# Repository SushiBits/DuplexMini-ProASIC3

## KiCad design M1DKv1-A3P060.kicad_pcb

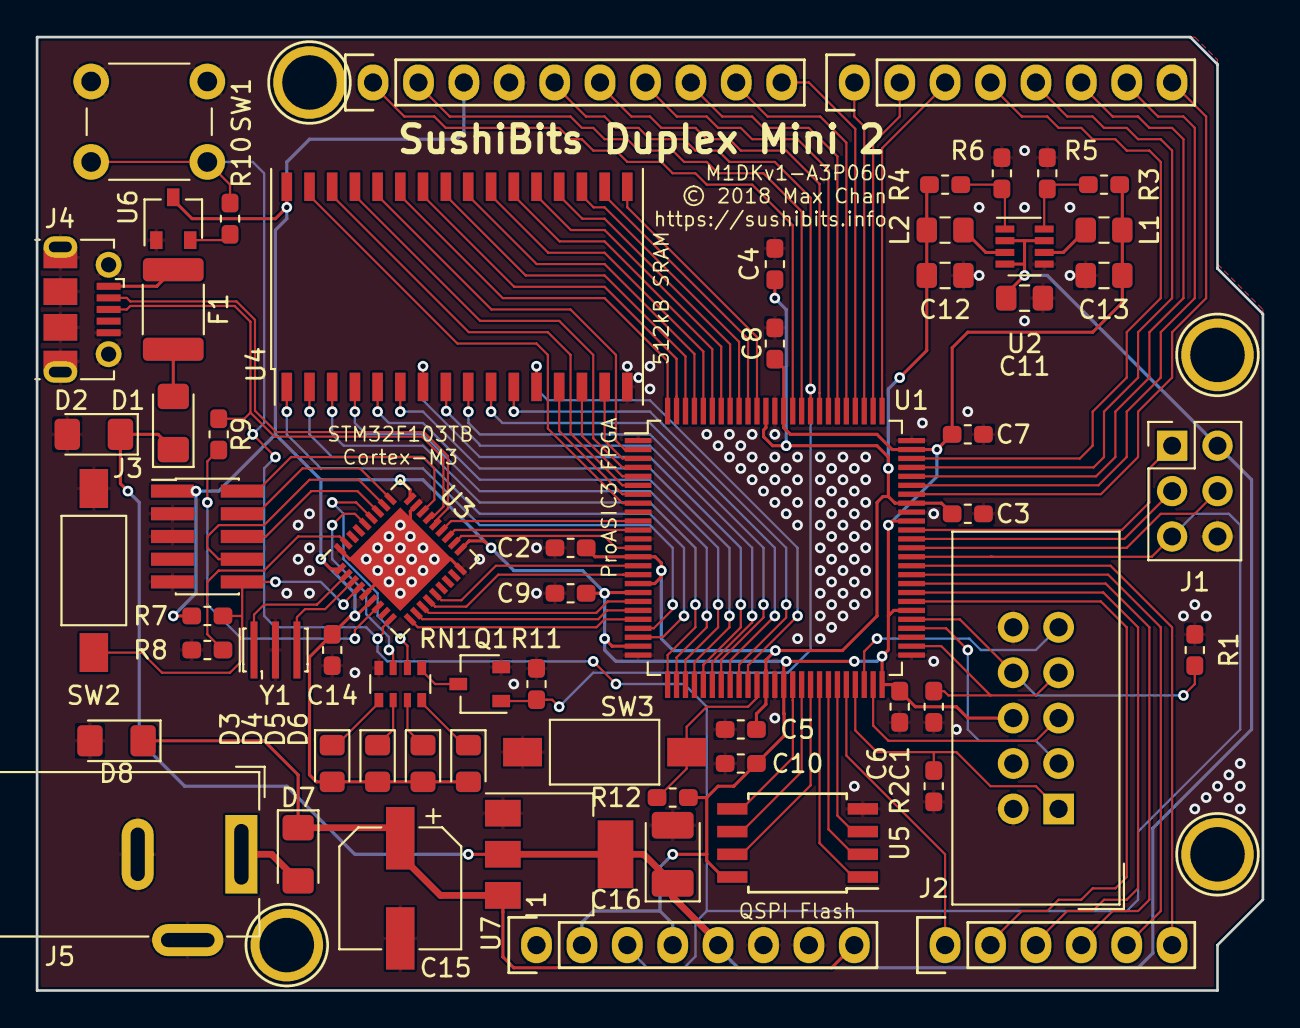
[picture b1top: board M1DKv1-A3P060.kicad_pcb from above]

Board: 2 copper layers, 68.6 x 53.3 mm, 65 parts (0 on the bottom side), 108 nets.

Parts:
C1: 1µ; C_0603_1608Metric_Pad1.05x0.95mm_HandSolder
C2, C3, C4, C5, C6, C7, C8, C9, C10, C14: 100n; C_0603_1608Metric_Pad1.05x0.95mm_HandSolder
C11: 10µ; C_0805_2012Metric_Pad1.15x1.40mm_HandSolder
C12, C13: 47µ; C_0805_2012Metric_Pad1.15x1.40mm_HandSolder
C15: 47µ; CP_Elec_6.3x5.3
C16: 220µ; CP_EIA-3528-12_Kemet-T_Pad1.50x2.35mm_HandSolder
D1: DSK14; D_1206_3216Metric_Pad1.42x1.75mm_HandSolder
D2: SMF5.0A; D_1206_3216Metric_Pad1.42x1.75mm_HandSolder
D3: Power; LED_0805_2012Metric_Pad1.15x1.40mm_HandSolder
D4: RX; LED_0805_2012Metric_Pad1.15x1.40mm_HandSolder
D5: TX; LED_0805_2012Metric_Pad1.15x1.40mm_HandSolder
D6: L; LED_0805_2012Metric_Pad1.15x1.40mm_HandSolder
D7: DSK10; D_1206_3216Metric_Pad1.42x1.75mm_HandSolder
D8: SMF12A; D_1206_3216Metric_Pad1.42x1.75mm_HandSolder
F1: 500mA; Fuse_1812_4532Metric_Pad1.30x3.40mm_HandSolder
J1: SPI; PinHeader_2x03_P2.54mm_Vertical
J2: FPGA; IDC-Header_2x05_P2.54mm_Vertical
J3: ARM; PinHeader_2x05_P1.27mm_Vertical_SMD
J4: USB; USB_Micro-B_Molex-105017-0001
J5: 12V; BarrelJack_Wuerth_6941xx301002
L1: 4.7µ; L_0805_2012Metric_Pad1.15x1.40mm_HandSolder
L2: 2.2µ; L_0805_2012Metric_Pad1.15x1.40mm_HandSolder
P1: Power; Socket_Strip_Arduino_1x08
P2: Analog; Socket_Strip_Arduino_1x06
P3: Digital; Socket_Strip_Arduino_1x10
P4: Digital; Socket_Strip_Arduino_1x08
P5, P6, P7, P8: CONN_01X01; Arduino_1pin
Q1: 2N7002; SOT-23W
R1, R2, R7, R8, R11, R12: 10k; R_0603_1608Metric_Pad1.05x0.95mm_HandSolder
R3, R4: 16k; R_0603_1608Metric_Pad1.05x0.95mm_HandSolder
R5: 3.6k; R_0603_1608Metric_Pad1.05x0.95mm_HandSolder
R6: 1.1k; R_0603_1608Metric_Pad1.05x0.95mm_HandSolder
R9: 1.5k; R_0603_1608Metric_Pad1.05x0.95mm_HandSolder
R10: 4.7k; R_0603_1608Metric_Pad1.05x0.95mm_HandSolder
RN1: 510; R_Array_Convex_4x0603
SW1: Reset; SW_PUSH_6mm
SW2: MCU Reset; SW_SPST_FSMSM
SW3: Action; SW_SPST_FSMSM
U1: A3P060-VQG100; TQFP-100_14x14mm_P0.5mm
U2: MP2122; SOT-23-8
U3: STM32F103TBUx; QFN-36-1EP_6x6mm_P0.5mm_EP4.1x4.1mm
U4: AS6C4008; TSOP-II-32_21.0x10.2mm_P1.27mm
U5: 25Q80; SOIJ-8_5.3x5.3mm_P1.27mm
U6: TCM809; SOT-23W
U7: LM1117-3.3; SOT-223-3_TabPin2
Y1: 16M; Resonator_SMD_muRata_CSTxExxV-3Pin_3.0x1.1mm_HandSoldering

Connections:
+1V5: C2.1, C3.1, C4.1, C5.1, C12.1, L2.2, R4.1, U1.14, U1.17, U1.37, U1.68, U1.89
+3V3: C6.1, C7.1, C8.1, C9.1, C10.1, C13.1, C14.2, D3.2, D4.2, D5.2, D6.2, J2.6, J3.1, L1.2, P1.2, P1.4, P3.3, R3.1, R7.1, R12.2, U1.18, U1.24, U1.39, U1.50, U1.56, U1.66, U1.74, U1.87, U3.1, U3.6, U3.19, U3.27, U4.32, U5.8, U6.3
+5V: C11.1, C16.1, D1.1, D2.1, J1.2, P1.5, U2.2, U2.4, U2.7, U7.2
+12V: C15.1, D7.1, D8.1, P1.8, U7.3
/0(Rx): P4.8, U1.69
/1(Tx): P4.7, U1.70
/2: P4.6, U1.71
/3: P4.5, U1.72
/4: P4.4, U1.73
/5: P4.3, U1.76
/6: P4.2, U1.77
/7: P4.1, U1.78
/8: P3.10, U1.79
/9: P3.9, U1.80
/10: P3.8, U1.81
/11: P3.7, U1.82
/12: P3.6, U1.83
/13: P3.5, Q1.1, R11.1, U1.84
/A0: P2.1, U1.46
/A1: P2.2, U1.57
/A2: P2.3, U1.58
/A3: P2.4, U1.59
/A4: P2.5, U1.60
/A5: P2.6, U1.61
/BUTTON: R12.1, SW3.1, U1.36
/CLK: U1.13, U3.20
/CRST: J3.10, R7.2, SW2.2, U3.4
/CTCK: J3.4, U3.28
/CTDI: J3.8, U3.29
/CTDO: J3.6, U3.30
/CTMS: J3.2, U3.25
/D+: J4.3, R9.1, U3.24
/D-: J4.2, U3.23
/FCS: U1.43, U5.1
/FHOLD: U1.42, U5.7
/FMISO: U1.44, U5.2
/FMOSI: U1.40, U5.5
/FSCK: U1.41, U5.6
/FTCK: J2.1, R2.1, U1.47
/FTDI: J2.9, U1.48
/FTDO: J2.3, U1.54
/FTMS: J2.5, U1.49
/FTRST: J2.8, R1.1, U1.55
/FVPUMP: C1.1, J2.7, U1.52
/FWP: U1.45, U5.3
/IRQ: U1.21, U3.10
/RA0: U1.35, U4.12
/RA1: U1.34, U4.11
/RA2: U1.33, U4.10
/RA3: U1.32, U4.9
/RA4: U1.31, U4.8
/RA5: U1.30, U4.7
/RA6: U1.29, U4.6
/RA7: U1.28, U4.5
/RA8: U1.100, U4.27
/RA9: U1.99, U4.26
/RA10: U1.96, U4.23
/RA11: U1.98, U4.25
/RA12: U1.27, U4.4
/RA13: U1.2, U4.28
/RA14: U1.26, U4.3
/RA15: U1.8, U4.31
/RA16: U1.23, U4.2
/RA17: U1.6, U4.30
/RA18: U1.22, U4.1
/RCS: U1.95, U4.22
/RD0: U1.7, U4.13
/RD1: U1.5, U4.14
/RD2: U1.3, U4.15
/RD3: U1.90, U4.17
/RD4: U1.91, U4.18
/RD5: U1.92, U4.19
/RD6: U1.93, U4.20
/RD7: U1.94, U4.21
/ROE: U1.97, U4.24
/RWR: U1.4, U4.29
/RXL: RN1.2, U3.31
/SCL: P3.1, U1.86
/SDA: P3.2, U1.85
/SMISO: J1.1, U1.65
/SMOSI: J1.4, U1.63
/SPIMISO: U1.16, U3.13
/SPIMOSI: U1.15, U3.14
/SPINSS: U1.20, U3.11
/SPISCK: U1.19, U3.12
/SSCK: J1.3, U1.64
/TXL: RN1.3, U3.32
/USRX: U1.10, U3.22
/USTX: U1.11, U3.21
/~RESET: J1.5, P1.3, R10.1, SW1.1, U1.62, U3.9
GND: C1.2, C2.2, C3.2, C4.2, C5.2, C6.2, C7.2, C8.2, C9.2, C10.2, C11.2, C12.2, C13.2, C14.1, C15.2, C16.2, D2.2, D8.2, J1.6, J2.2, J2.10, J3.3, J3.5, J3.9, J4.5, J4.6, J5.2, J5.3, P1.6, P1.7, P3.4, Q1.2, R1.2, R2.2, R5.2, R6.2, R8.2, R11.2, RN1.4, SW1.2, SW2.1, SW3.2, U1.1, U1.9, U1.12, U1.25, U1.38, U1.51, U1.67, U1.75, U1.88, U2.5, U3.5, U3.18, U3.26, U3.36, U3.37, U4.16, U5.4, U6.1, U7.1, Y1.2
unnamed: D1.2, F1.1
unnamed: D3.1, RN1.5
unnamed: D4.1, RN1.6
unnamed: D5.1, RN1.7
unnamed: D6.1, RN1.8
unnamed: D7.2, J5.1
unnamed: F1.2, J4.1
unnamed: L1.1, U2.6
unnamed: L2.1, U2.3
unnamed: Q1.3, RN1.1
unnamed: R3.2, R5.1, U2.8
unnamed: R4.2, R6.1, U2.1
unnamed: R8.1, U3.35
unnamed: R9.2, U3.7
unnamed: R10.2, U6.2
unnamed: U3.2, Y1.1
unnamed: U3.3, Y1.3

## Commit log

2018-11-27 Ignore release fiels and macOS junk
2018-11-27 Remove the release files

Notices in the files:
M1DKv1-A3P060.kicad_pcb:
© 2018 Max Chan
